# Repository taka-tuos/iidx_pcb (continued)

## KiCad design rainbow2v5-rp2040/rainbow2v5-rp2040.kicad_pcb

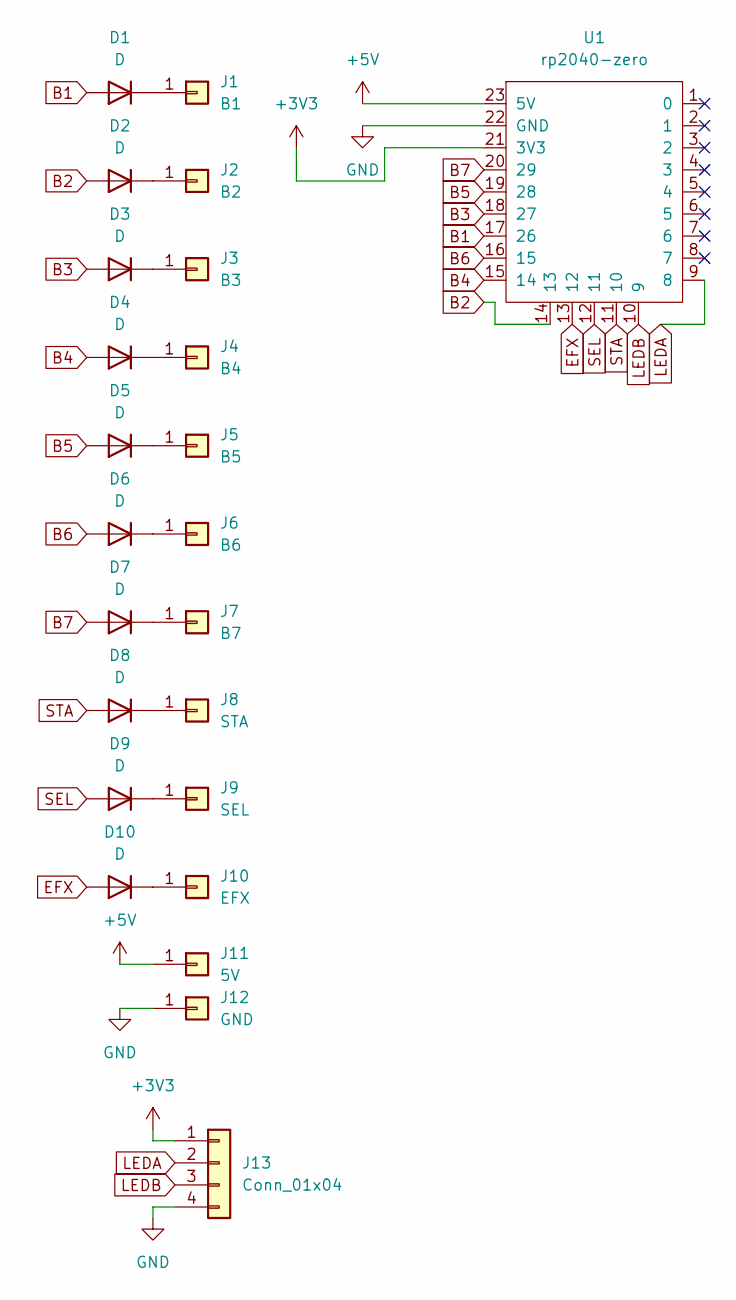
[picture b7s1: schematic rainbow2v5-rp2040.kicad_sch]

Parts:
D1, D2, D3, D4, D5, D6, D7, D8, D9, D10: D; D_DO-35_SOD27_P2.54mm_Vertical_AnodeUp
J1: B1; DJ610-4.8x14
J2: B2; DJ610-4.8x14
J3: B3; DJ610-4.8x14
J4: B4; DJ610-4.8x14
J5: B5; DJ610-4.8x14
J6: B6; DJ610-4.8x14
J7: B7; DJ610-4.8x14
J8: STA; DJ610-4.8x14
J9: SEL; DJ610-4.8x14
J10: EFX; DJ610-4.8x14
J11: 5V; DJ610-4.8x14
J12: GND; DJ610-4.8x14
J13: Conn_01x04; JST_XH_B4B-XH-A_1x04_P2.50mm_Vertical
U1: rp2040-zero; rp2040-zero-smd

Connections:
+3V3: J13.1, U1.21 (3V3)
+5V: J11.1, U1.23 (5V)
B1: D1.2 (A), U1.17 (26)
B2: D2.2 (A), U1.14 (13)
B3: D3.2 (A), U1.18 (27)
B4: D4.2 (A), U1.15 (14)
B5: D5.2 (A), U1.19 (28)
B6: D6.2 (A), U1.16 (15)
B7: D7.2 (A), U1.20 (29)
EFX: D10.2 (A), U1.13 (12)
GND: J12.1, J13.4, U1.22 (GND)
LEDA: J13.2, U1.9 (8)
LEDB: J13.3, U1.10 (9)
unnamed: D1.1 (K), J1.1
unnamed: D2.1 (K), J2.1
unnamed: D3.1 (K), J3.1
unnamed: D4.1 (K), J4.1
unnamed: D5.1 (K), J5.1
unnamed: D6.1 (K), J6.1
unnamed: D7.1 (K), J7.1
unnamed: D8.1 (K), J8.1
unnamed: D9.1 (K), J9.1
unnamed: D10.1 (K), J10.1
SEL: D9.2 (A), U1.12 (11)
STA: D8.2 (A), U1.11 (10)

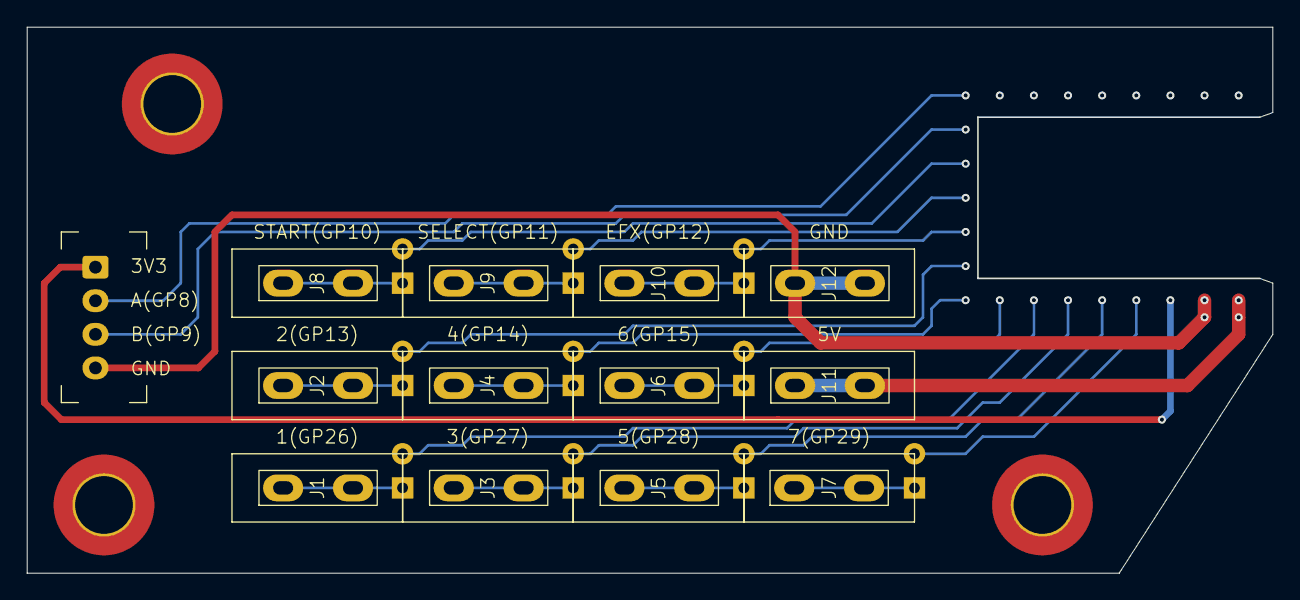
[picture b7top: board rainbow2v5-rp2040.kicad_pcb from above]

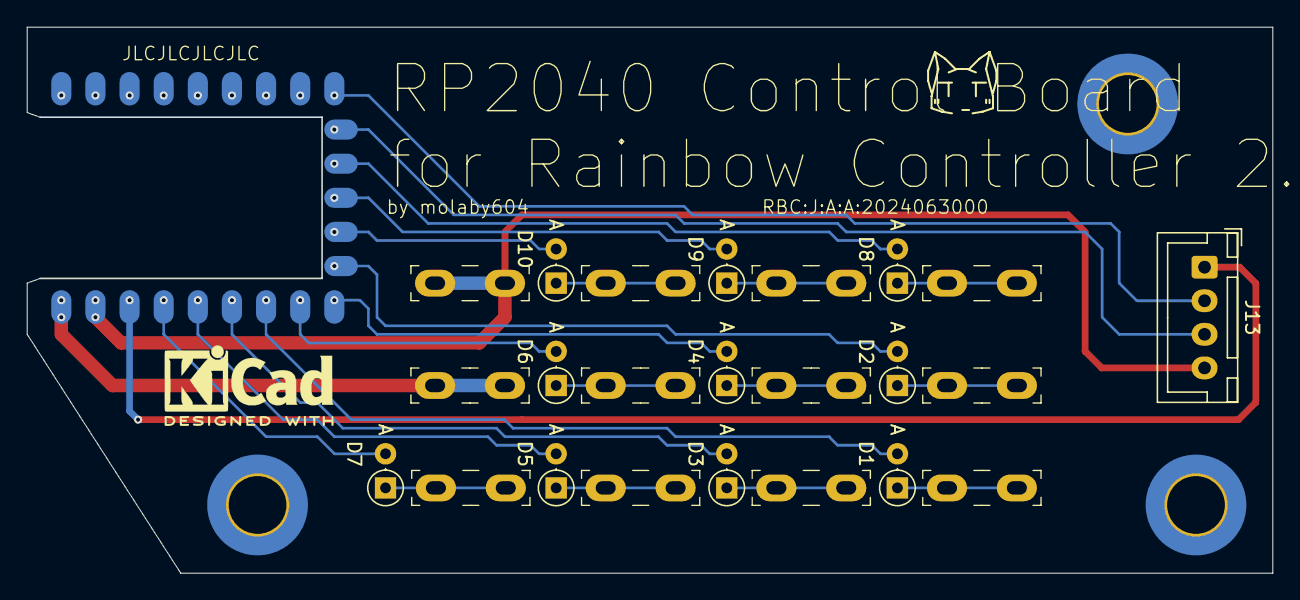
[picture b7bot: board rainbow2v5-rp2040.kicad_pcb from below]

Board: 2 copper layers, 92.7 x 40.6 mm, 24 parts (12 on the bottom side), 25 nets.

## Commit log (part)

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2024-06-30 add rainbow2v5-rp2040
2024-06-30 Create LICENSE
2024-07-10 add iidx-refine
2024-08-18 add rainbow2-rp2040
2025-01-20 update iidx_pcb_rev2
2025-02-10 update footprints for rev2
